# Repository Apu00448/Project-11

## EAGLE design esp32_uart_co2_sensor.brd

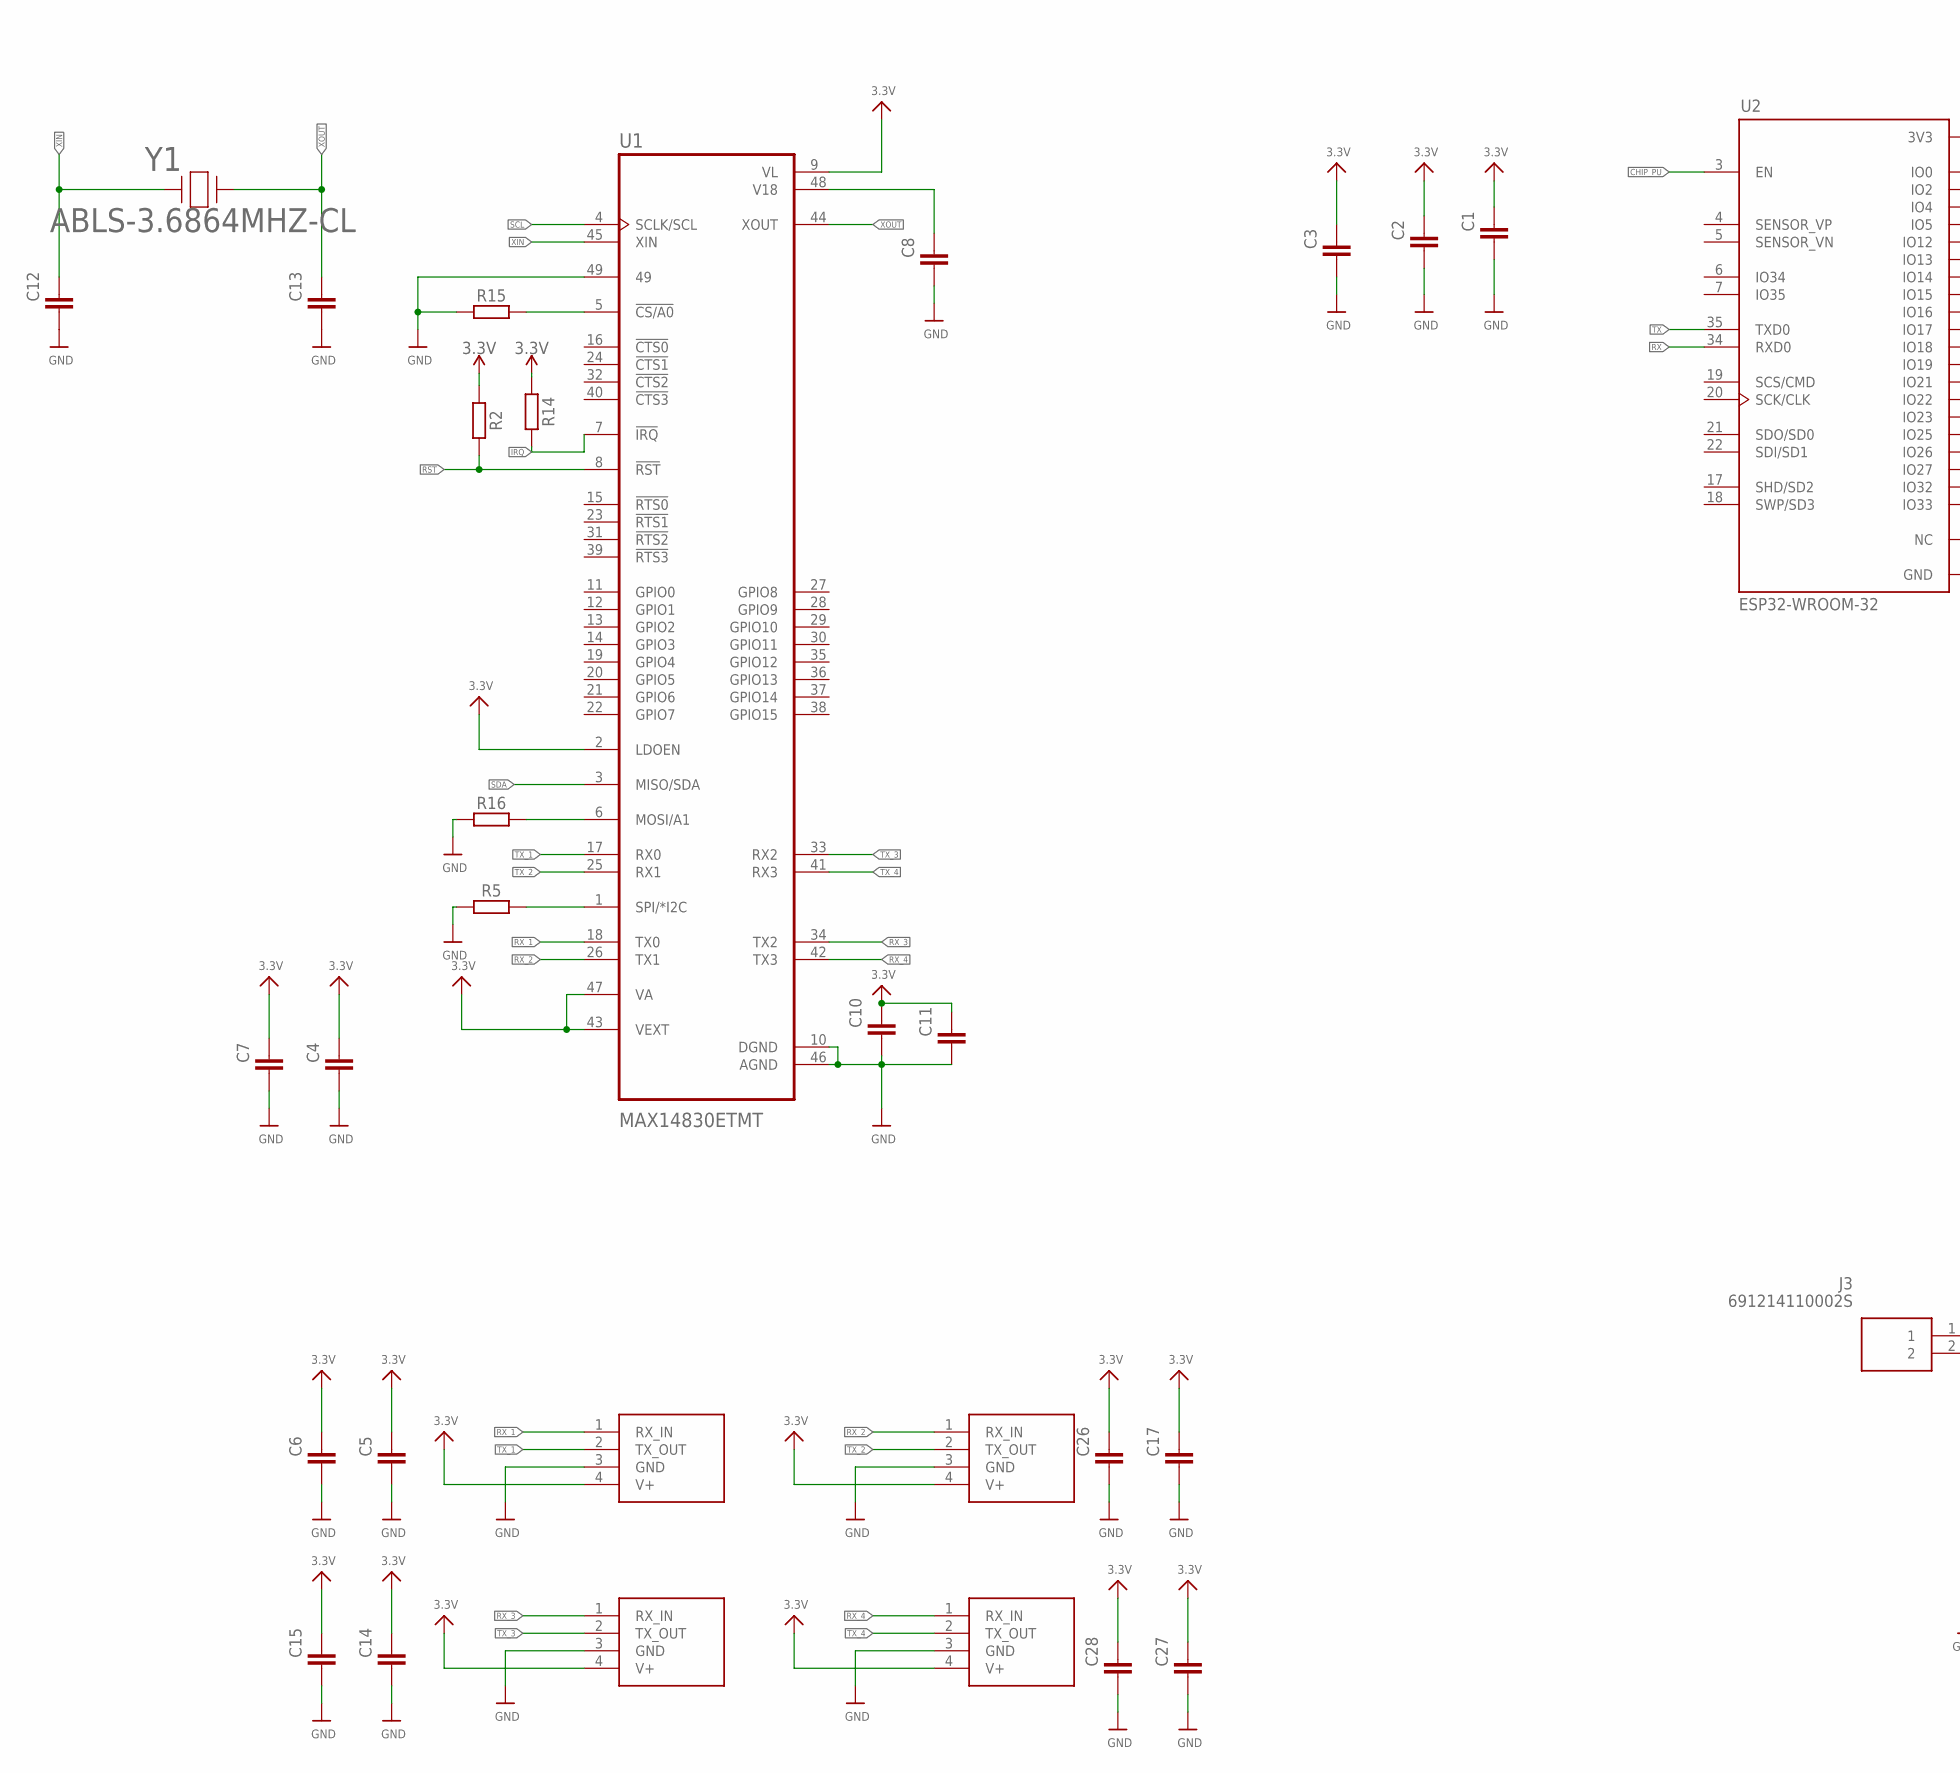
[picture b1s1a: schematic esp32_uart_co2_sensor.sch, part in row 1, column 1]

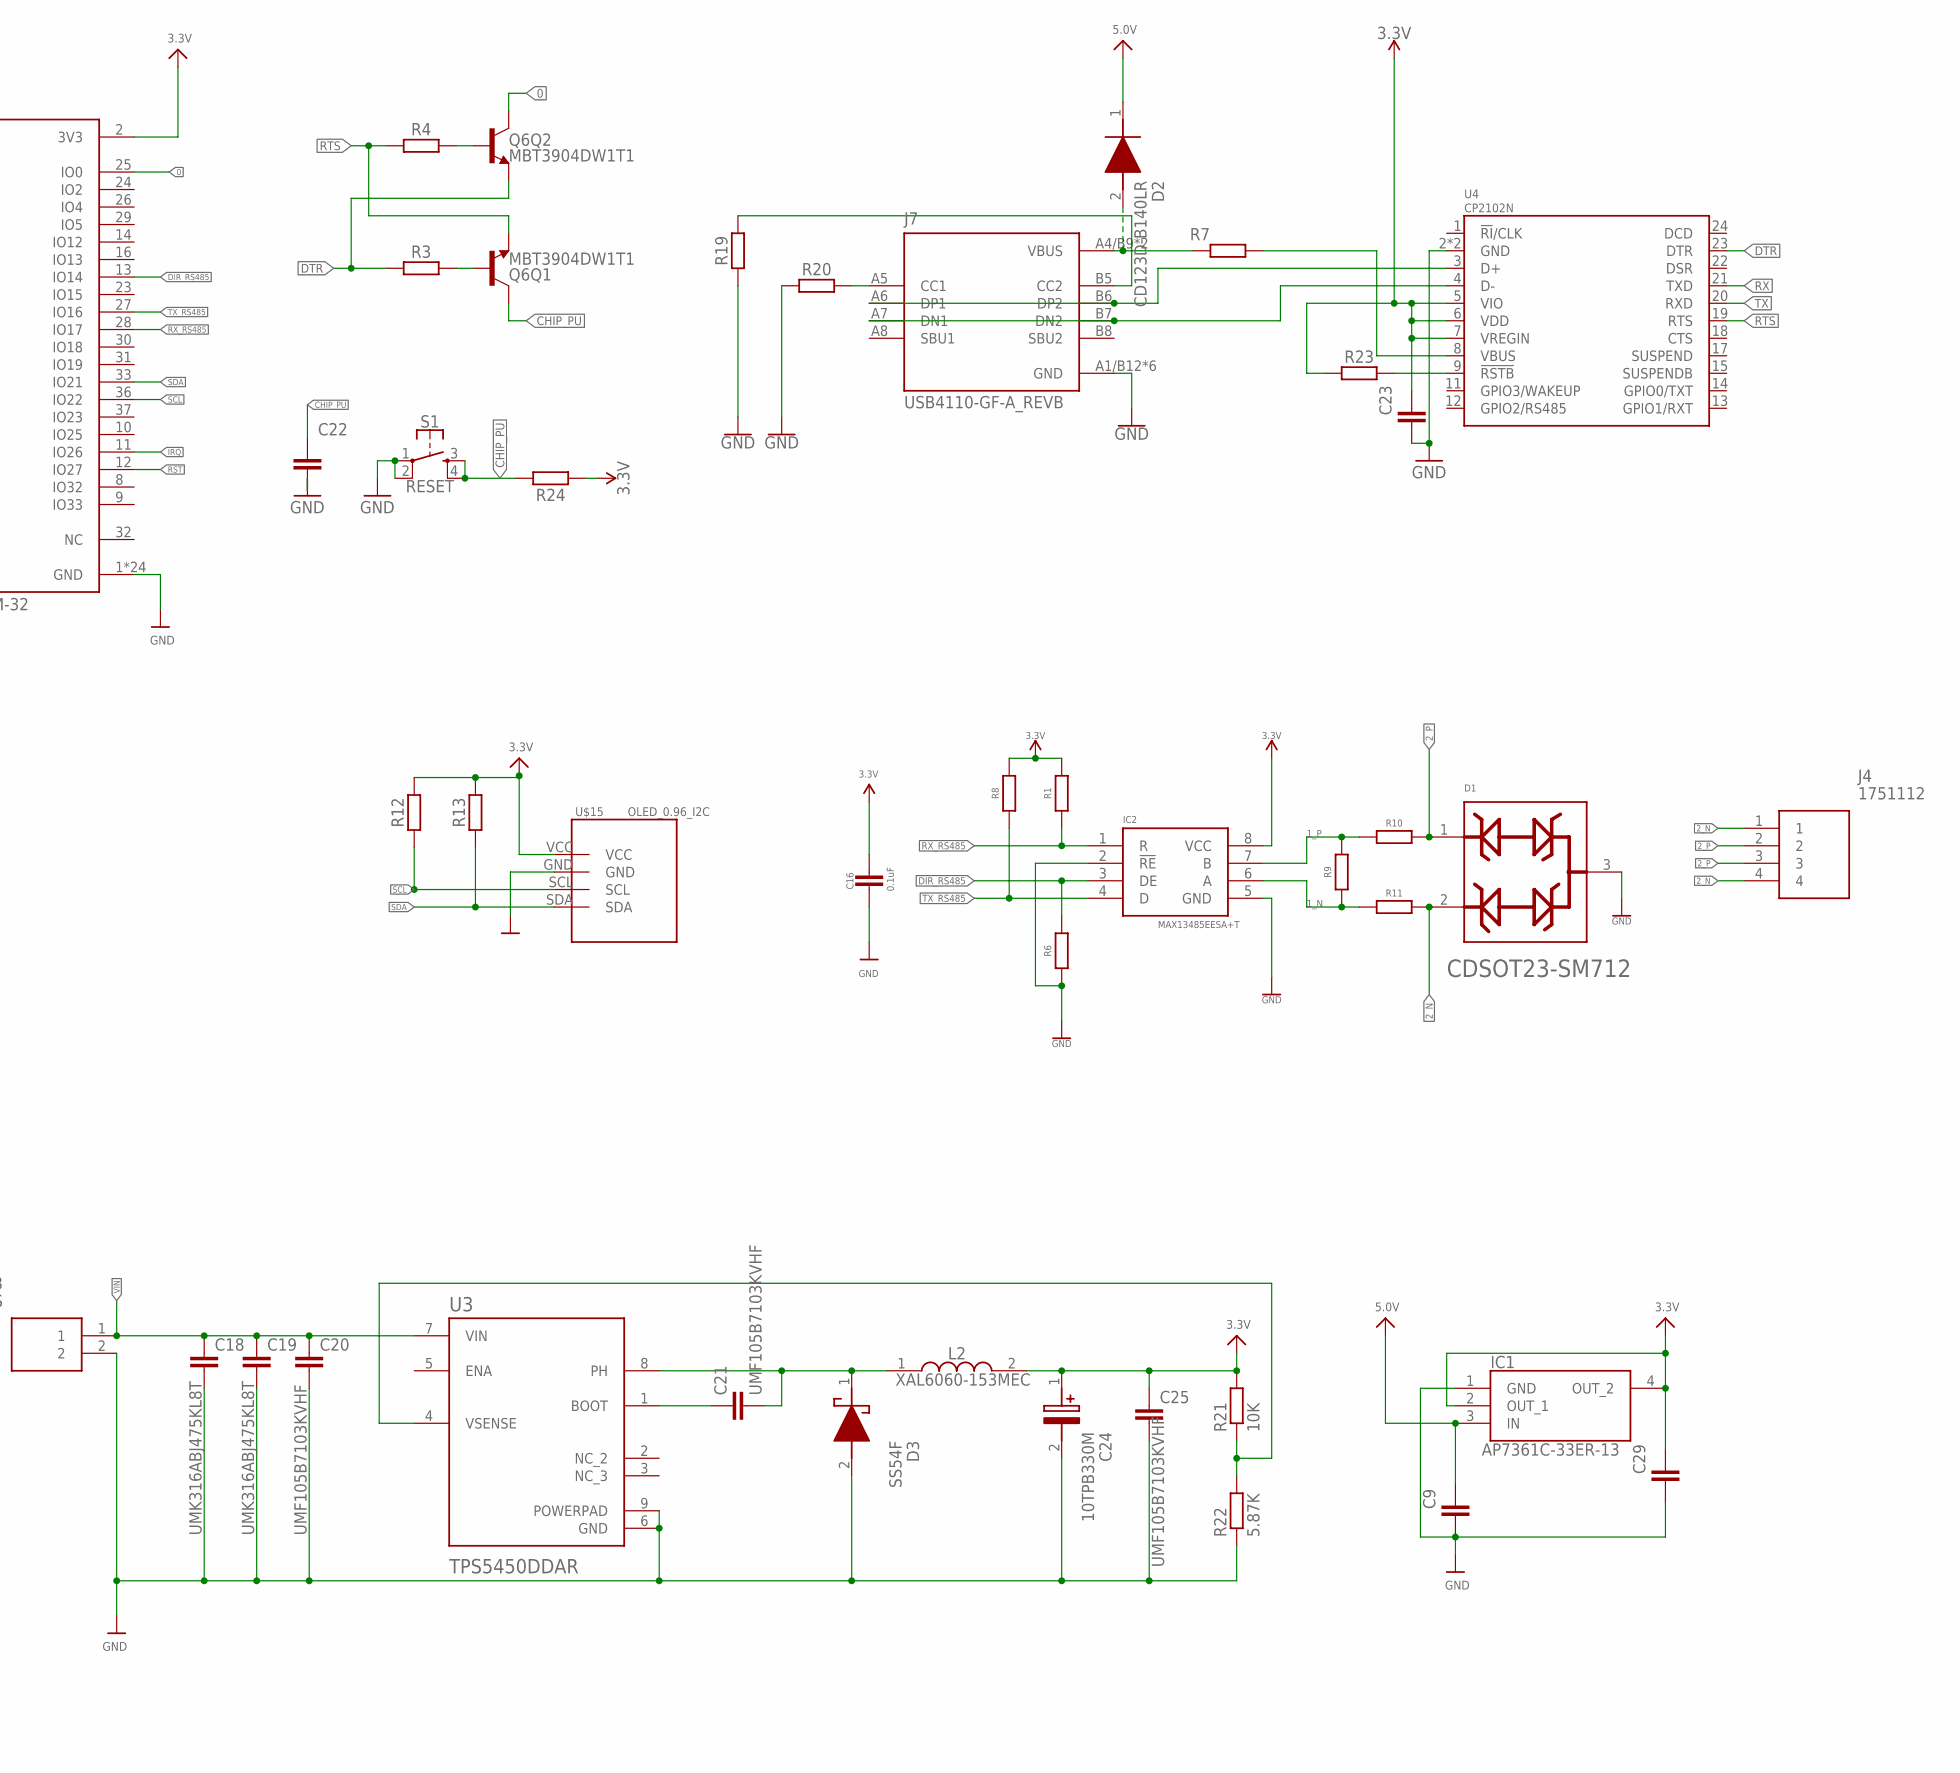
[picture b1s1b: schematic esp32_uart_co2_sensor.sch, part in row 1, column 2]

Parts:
C1, C6, C7, C15, C23, C26, C28: 10uF; C0402
C2: 0.1uF; C0402
C3, C4, C5, C8, C10, C11, C14, C17, C27: 1uF; C0402
C9, C29: 4.7uF; C0402
C12, C13: 18pF; C0402
C16: 0.1uF; 0402-TIGHT
C18, C19: UMK316ABJ475KL8T; C1206
C20, C21, C25: UMF105B7103KVHF; C0402
C22: 1.0uF; C0402
C24: 10TPB330M; CAPPM7343X400N
D1: BOURNS_INC._CDSOT23-SM712BOURNS_INC._CDSOT23-SM71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; BOURNS_INC._CDSOT23-SM712_0
D2: CD123D-B140LR; CD123DB140LR
D3: SS54F; SODFL4626X130N
IC1: AP7361C-33ER-13; SOT230P700X180-4N
IC2: MAX13485EESA+T; SOIC127P600X175-8N
J3: 691214110002S
J4: 1751112
J7: USB4110-GF-A_REVB; GCT_USB4110-GF-A_REVB
L2: XAL6060-153MEC; XAL6060153MEC
Q6: MBT3904DW1T1; SC70-6
R1, R8: 2.2k; R0402
R2, R3, R4, R5, R12, R13, R14, R15, R16, R24: 10k; R0402
R6: 2.2k; R0603
R7: 10; R0603
R9: 120R; R0603
R10, R11: 10Ω; R0402
R19, R20: 5.1k; R0402
R21: 10K; R0402
R22: 5.87K; R0402
R23: 1k; R0402
S1: RESET; TACTILE_SWITCH_SMD_4.6X2.8MM
SEN1, SEN2, SEN3, SEN4: SPRINTIR-6S-20
U1: MAX14830ETMT; QFN50P700X700X80-49N
U2: ESP32-WROOM-32; MODULE_ESP32-WROOM-32
U3: TPS5450DDAR; CONV_TPS5450DDAR
U4: CP2102N; QFN24
U$15: OLED_0.96_I2C
Y1: ABLS-3.6864MHZ-CL; ABLS_SERIES_ABR

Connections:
0: Q6.6 (C), U2.25 (IO0)
1_N: IC2.6 (A), R9.1, R11.1
1_P: IC2.7 (B), R9.2, R10.1
2_N: D1.2, J4.1, J4.4, R11.2
2_P: D1.1, J4.2, J4.3, R10.2
3.3V: C1.1, C2.1, C3.1, C4.1, C5.1, C6.1, C7.1, C10.1, C11.1, C14.1, C15.1, C16.1, C17.1, C23.1, C24.1 (+), C25.1, C26.1, C27.1, C28.1, C29.1, IC1.2 (OUT_1), IC1.4 (OUT_2), IC2.8 (VCC), L2.2, R1.2, R2.1, R8.2, R12.2, R13.2, R14.1, R21.2, R23.1, R24.1, SEN1.4 (V+), SEN2.4 (V+), SEN3.4 (V+), SEN4.4 (V+), U1.2 (LDOEN), U1.9 (VL), U1.43 (VEXT), U1.47 (VA), U2.2 (3V3), U4.5 (VIO), U4.6 (VDD), U4.7 (VREGIN), U$15.VCC
5.0V: C9.1, D2.1 (K), IC1.3 (IN)
CHIP_PU: C22.1, Q6.3 (C), R24.2, S1.3, S1.4, U2.3 (EN)
CS: R15.2, U1.5 (!CS/A0)
DIR_RS485: IC2.3 (DE), R6.2, U2.13 (IO14)
DTR: Q6.1 (E), R3.1, U4.23 (DTR)
GND: C1.2, C2.2, C3.2, C4.2, C5.2, C6.2, C7.2, C8.2, C9.2, C10.2, C11.2, C12.2, C13.2, C14.2, C15.2, C16.2, C17.2, C18.2, C19.2, C20.2, C22.2, C23.2, C24.2 (-), C25.2, C26.2, C27.2, C28.2, C29.2, D1.3, D3.2 (A), IC1.1 (GND), IC2.2 (!RE), IC2.5 (GND), J3.2, J7.A1/B12 (GND), J7.B1/A12 (GND), J7.S1 (GND), J7.S2 (GND), J7.S3 (GND), J7.S4 (GND), R5.1, R6.1, R15.1, R16.1, R19.1, R20.1, R22.1, S1.1, S1.2, SEN1.3 (GND), SEN2.3 (GND), SEN3.3 (GND), SEN4.3 (GND), U1.10 (DGND), U1.46 (AGND), U1.49, U2.1 (GND), U2.15 (GND), U2.38 (GND), U2.39_1 (GND), U2.39_2 (GND), U2.39_3 (GND), U2.39_4 (GND), U2.39_5 (GND), U2.39_6 (GND), U2.39_7 (GND), U2.39_8 (GND), U2.39_9 (GND), U2.39_10 (GND), U2.39_11 (GND), U2.39_12 (GND), U2.39_13 (GND), U2.39_14 (GND), U2.39_15 (GND), U2.39_16 (GND), U2.39_17 (GND), U2.39_18 (GND), U2.39_19 (GND), U2.39_20 (GND), U2.39_21 (GND), U3.6 (GND), U3.9 (POWERPAD), U4.2 (GND), U4.PAD (GND), U$15.GND
IRQ: R14.2, U1.7 (!IRQ), U2.11 (IO26)
unnamed: C8.1, U1.48 (V18)
unnamed: R16.2, U1.6 (MOSI/A1)
unnamed: R5.2, U1.1 (SPI/*I2C)
unnamed: J7.A6 (DP1), J7.B6 (DP2), U4.3 (D+)
unnamed: J7.A7 (DN1), J7.B7 (DN2), U4.4 (D-)
unnamed: J7.A5 (CC1), R20.2
unnamed: J7.B5 (CC2), R19.2
unnamed: C21.1, U3.1 (BOOT)
unnamed: C21.2, D3.1 (K), L2.1, U3.8 (PH)
unnamed: D2.2 (A), J7.A4/B9 (VBUS), J7.B4/A9 (VBUS), R7.1
unnamed: R21.1, R22.2, U3.4 (VSENSE)
unnamed: Q6.5 (B), R3.2
unnamed: Q6.2 (B), R4.2
unnamed: R23.2, U4.9 (!RSTB)
unnamed: R7.2, U4.8 (VBUS)
RST: R2.2, U1.8 (!RST), U2.12 (IO27)
RTS: Q6.4 (E), R4.1, U4.19 (RTS)
RX: U2.34 (RXD0), U4.21 (TXD)
RX_1: SEN1.1 (RX_IN), U1.18 (TX0)
RX_2: SEN2.1 (RX_IN), U1.26 (TX1)
RX_3: SEN3.1 (RX_IN), U1.34 (TX2)
RX_4: SEN4.1 (RX_IN), U1.42 (TX3)
RX_RS485: IC2.1 (R), R1.1, U2.28 (IO17)
SCL: R12.1, U1.4 (SCLK/SCL), U2.36 (IO22), U$15.SCL
SDA: R13.1, U1.3 (MISO/SDA), U2.33 (IO21), U$15.SDA
TX: U2.35 (TXD0), U4.20 (RXD)
TX_1: SEN1.2 (TX_OUT), U1.17 (RX0)
TX_2: SEN2.2 (TX_OUT), U1.25 (RX1)
TX_3: SEN3.2 (TX_OUT), U1.33 (RX2)
TX_4: SEN4.2 (TX_OUT), U1.41 (RX3)
TX_RS485: IC2.4 (D), R8.1, U2.27 (IO16)
VIN: C18.1, C19.1, C20.1, J3.1, U3.7 (VIN)
XIN: C12.1, U1.45 (XIN), Y1.1
XOUT: C13.1, U1.44 (XOUT), Y1.2

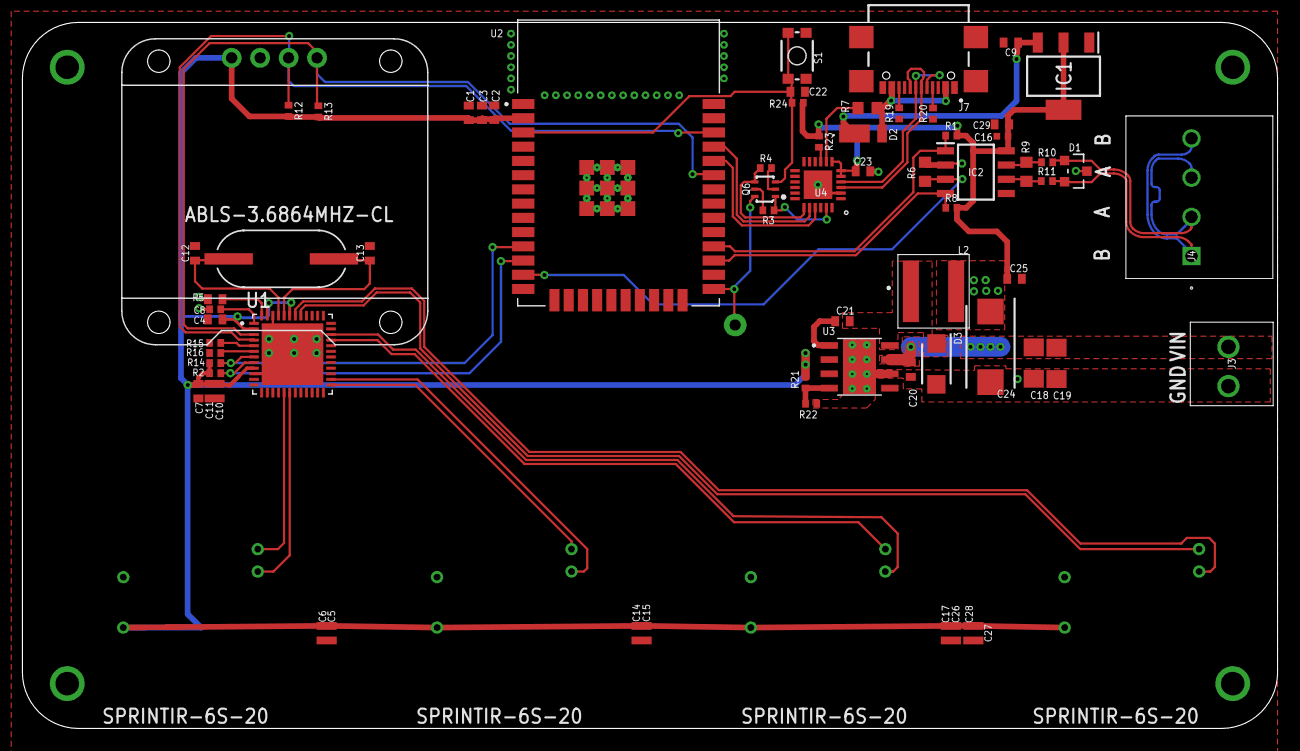
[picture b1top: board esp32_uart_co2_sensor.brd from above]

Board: 2 copper layers, 112.0 x 63.0 mm, 72 parts (0 on the bottom side), 47 nets.

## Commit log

2024-01-03 ESP32_UART_CO2 _Sensor-- Eagle

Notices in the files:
parts and their libraries:
SparkFun-Capacitors: Licensing: Creative Commons ShareAlike 4.0 International - https://creativecommons.org/licenses/by-sa/4.0
COPYRIGHT: Copyright (C) 2022 Ultra Librarian. All rights reserved.
